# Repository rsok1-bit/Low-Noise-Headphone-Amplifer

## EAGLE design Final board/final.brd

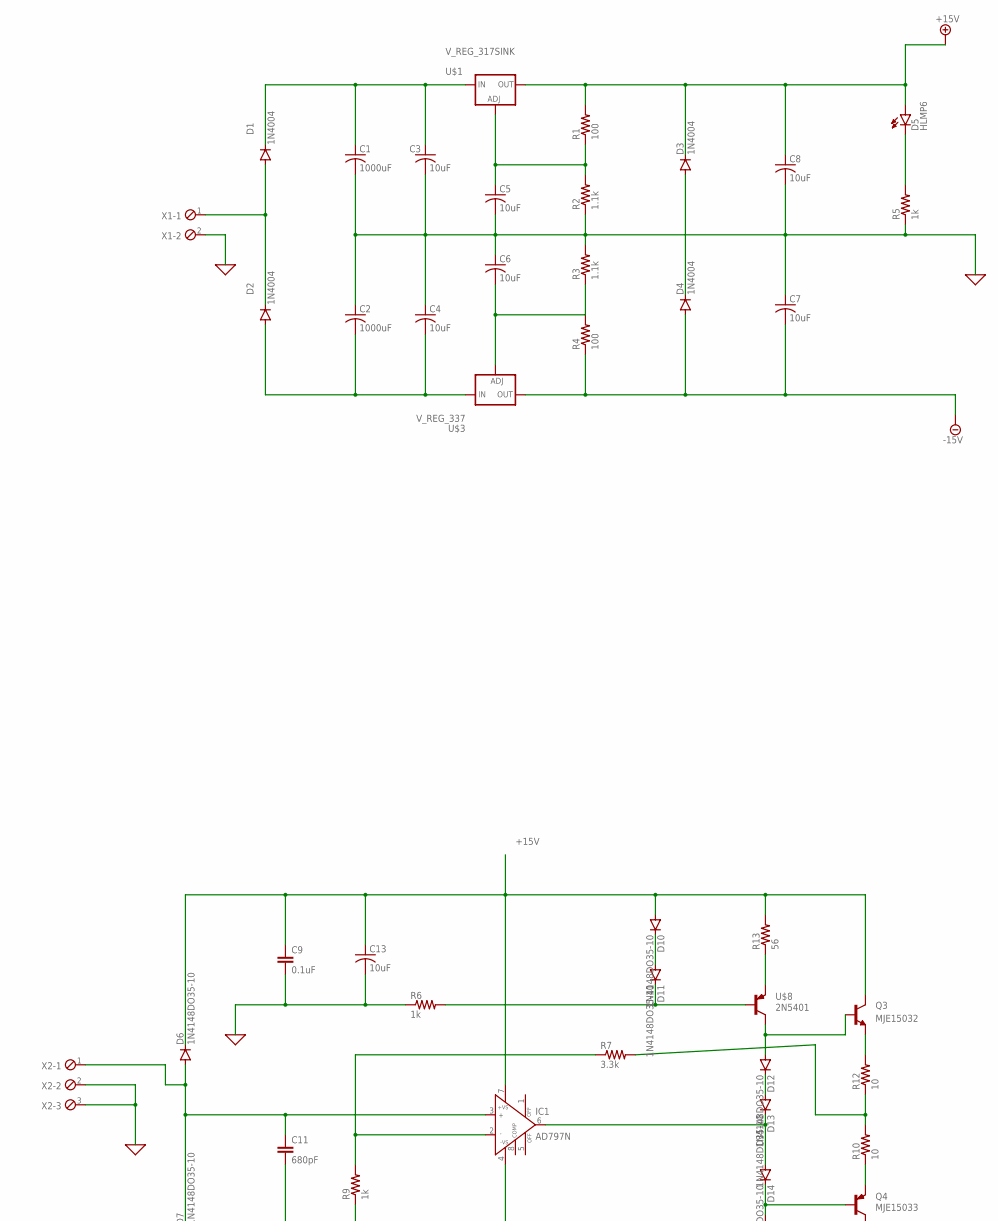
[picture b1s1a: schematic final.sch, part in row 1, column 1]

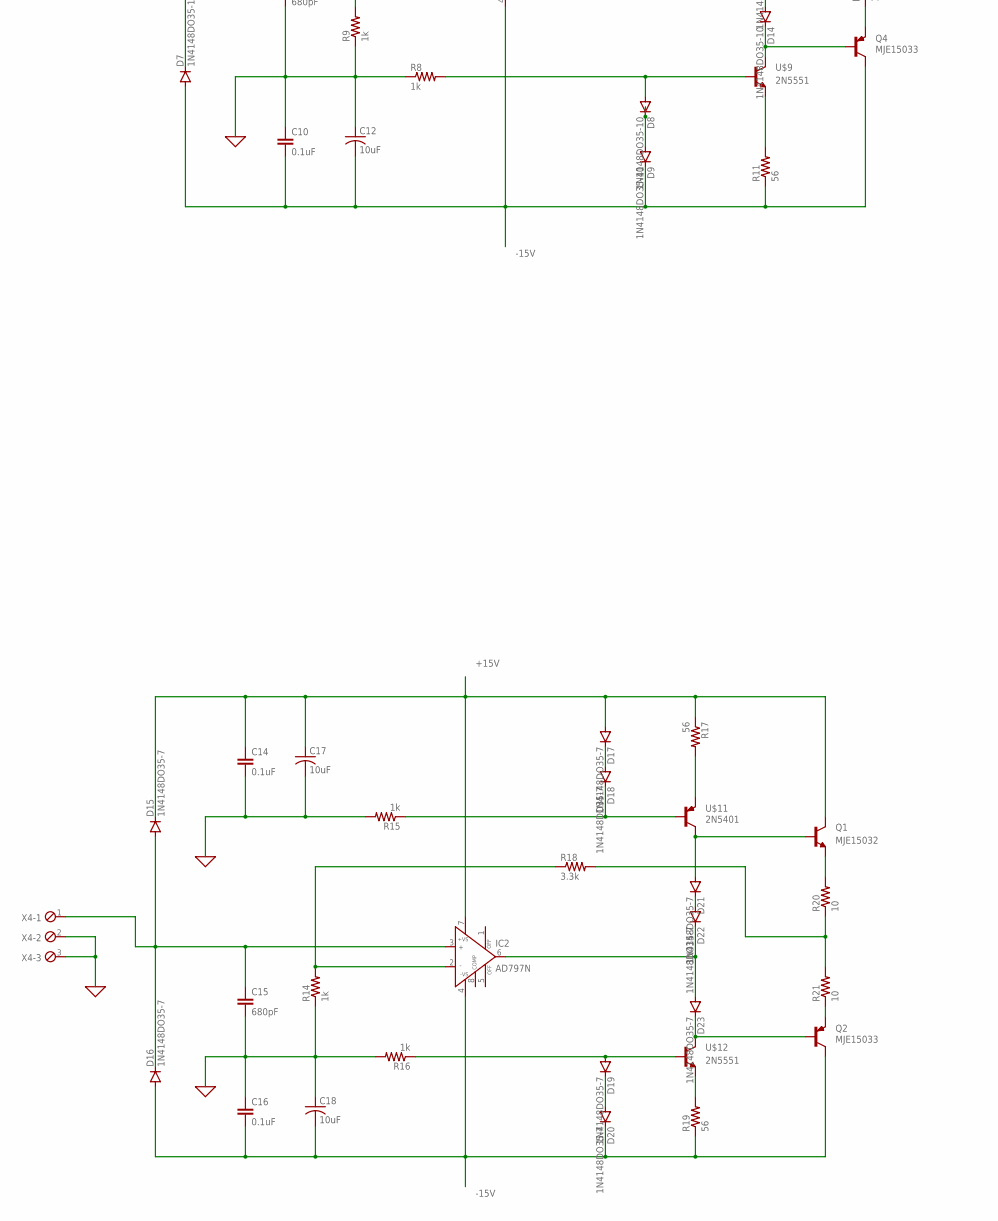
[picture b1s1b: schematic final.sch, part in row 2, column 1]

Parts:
C1, C2: 1000uF; C050-024X044
C3, C4, C5, C6, C7, C8, C12, C13, C17, C18: 10uF; C050-024X044
C9, C10, C14, C16: 0.1uF; C2.5-3
C11, C15: 680pF; C2.5-3
D1, D2, D3, D4: 1N4004; DO41-10
D5: HLMP6
D6, D7, D8, D9, D10, D11, D12, D13, D14: 1N4148DO35-10; DO35-10
D15, D16, D17, D18, D19, D20, D21, D22, D23: 1N4148DO35-7; DO35-7
IC1, IC2: AD797N; DIL08
Q1, Q3: MJE15032; TO220V
Q2, Q4: MJE15033; TO220V
R1, R4: 100; 0204/7
R2, R3: 1.1k; 0204/7
R5, R6, R8, R9, R14, R15, R16: 1k; 0204/7
R7, R18: 3.3k; 0204/7
R10, R12, R20, R21: 10; 0204/7
R11, R13, R17, R19: 56; 0204/7
U$1: V_REG_317SINK; TO220-ADJ
U$3: V_REG_337; TO220-ADJ-NEG
U$8, U$11: 2N5401
U$9, U$12: 2N5551
X1: MPT2; 2POL254
X2, X4: MPT3; 3POL254

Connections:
0: C1.2, C2.1, C3.2, C4.1, C5.2, C6.1, C7.1, C8.2, C9.2, C10.1, C11.2, C12.1, C13.2, C14.2, C15.2, C16.1, C17.2, C18.1, R2.1, R3.2, R5.1, R6.1, R8.1, R9.1, R14.1, R15.2, R16.2, X1.2, X2.2, X2.3, X4.2, X4.3
+15V: C8.1, C9.1, C13.1, C14.1, C17.1, D3.C, D5.A, D6.C, D10.A, D15.C, D17.A, IC1.7 (+VS), IC2.7 (+VS), Q1.2 (C), Q3.2 (C), R1.2, R13.2, R17.1, U$1.OUT
-15V: C7.2, C10.2, C12.2, C16.2, C18.2, D4.A, D7.A, D9.C, D16.A, D20.C, IC1.4 (-VS), IC2.4 (-VS), Q2.2 (C), Q4.2 (C), R4.1, R11.1, R19.1, U$3.OUT
unnamed: D1.A, D2.C, X1.1
unnamed: C2.2, C4.2, D2.A, U$3.IN
unnamed: C1.1, C3.1, D1.C, U$1.IN
unnamed: C11.1, D6.A, D7.C, IC1.3 (IN+), X2.1
unnamed: D11.C, R6.2, U$8.B
unnamed: D10.C, D11.A
unnamed: R13.1, U$8.C (E)
unnamed: D8.A, R8.2, U$9.B
unnamed: C5.1, R1.1, R2.2, U$1.ADJ
unnamed: D8.C, D9.A
unnamed: C6.2, R3.1, R4.2, U$3.ADJ
unnamed: D3.A, D4.C
unnamed: R11.2, U$9.E
unnamed: D5.K, R5.2
unnamed: D12.A, Q3.1 (B), U$8.E (C)
unnamed: D12.C, D13.A
unnamed: D13.C, D14.A, IC1.6 (OUT)
unnamed: D14.C, Q4.1 (B), U$9.C
unnamed: IC1.2 (IN-), R7.1, R9.2
unnamed: Q3.3 (E), R12.2
unnamed: R7.2, R10.2, R12.1
unnamed: Q4.3 (E), R10.1
unnamed: D18.C, R15.1, U$11.B
unnamed: D17.C, D18.A
unnamed: R17.2, U$11.C (E)
unnamed: D21.A, Q1.1 (B), U$11.E (C)
unnamed: D19.C, D20.A
unnamed: C15.1, D15.A, D16.C, IC2.3 (IN+), X4.1
unnamed: IC2.2 (IN-), R14.2, R18.1
unnamed: D19.A, R16.1, U$12.B
unnamed: R19.2, U$12.E
unnamed: D23.C, Q2.1 (B), U$12.C
unnamed: D22.C, D23.A, IC2.6 (OUT)
unnamed: D21.C, D22.A
unnamed: Q2.3 (E), R21.1
unnamed: R18.2, R20.1, R21.2
unnamed: Q1.3 (E), R20.2

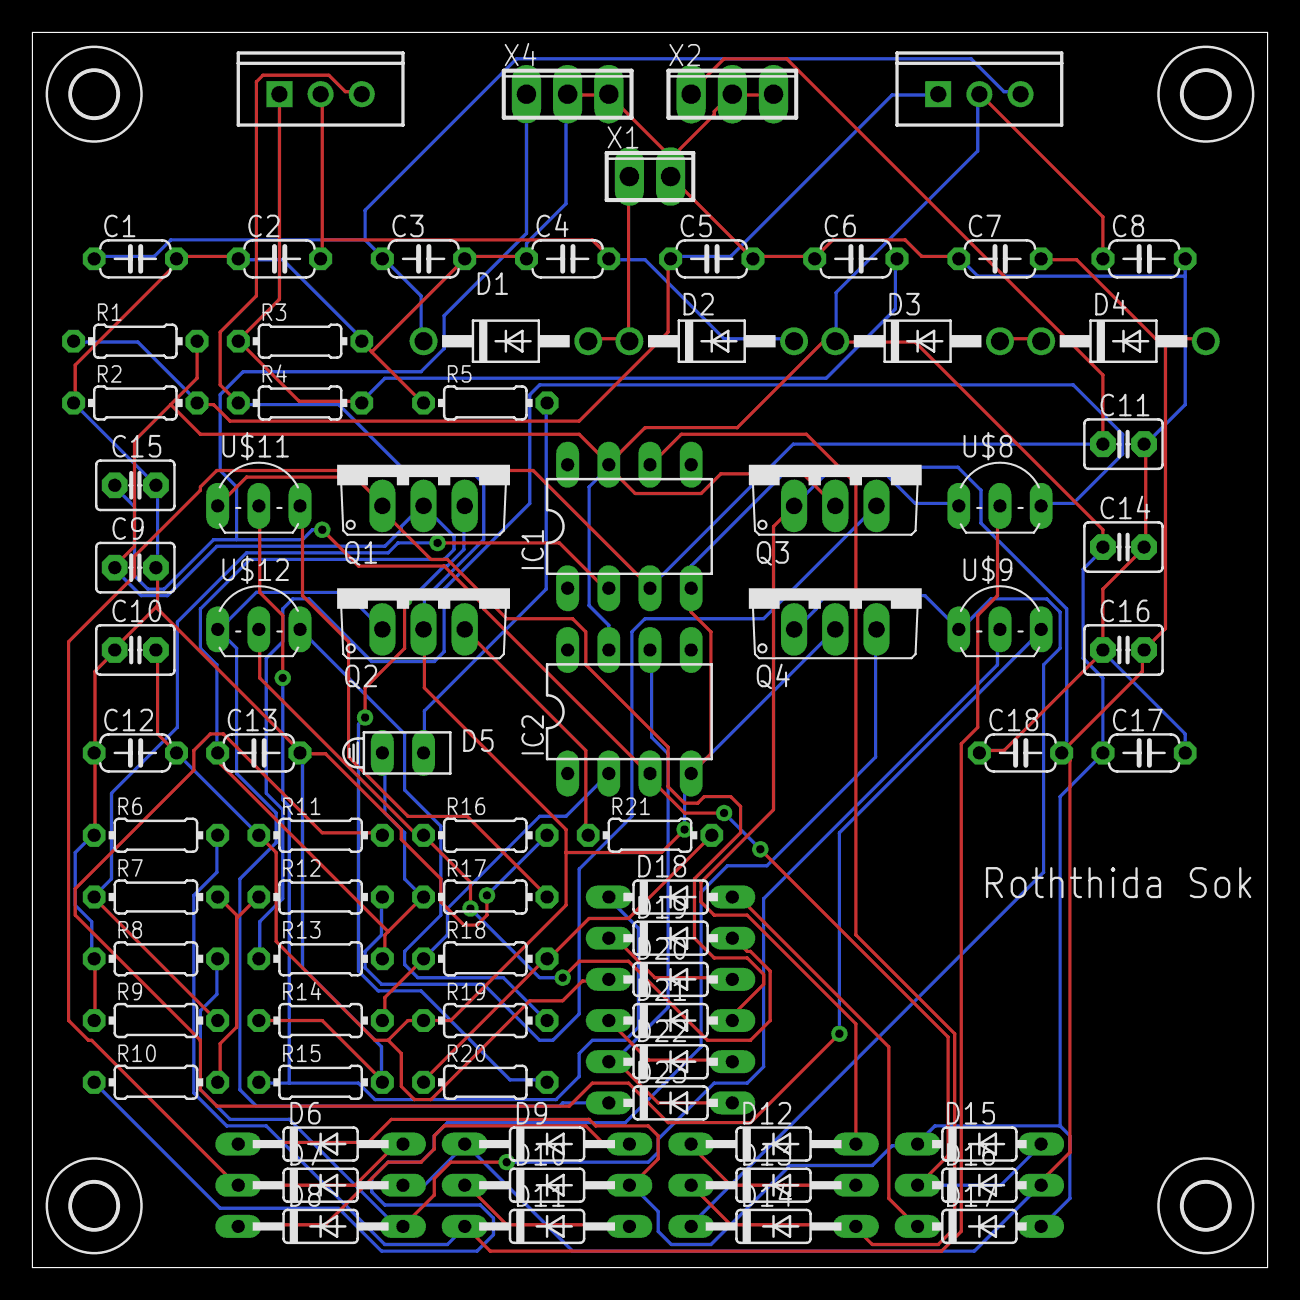
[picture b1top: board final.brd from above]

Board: 2 copper layers, 76.2 x 76.2 mm, 81 parts (0 on the bottom side), 40 nets.

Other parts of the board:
U$2, U$4, U$5, U$6: 2,8

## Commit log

2025-05-30 reupload of project
2025-05-30 pcb board
